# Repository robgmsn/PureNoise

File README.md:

View this project on [CADLAB.io](https://cadlab.io/project/24192). 

# PureNoise

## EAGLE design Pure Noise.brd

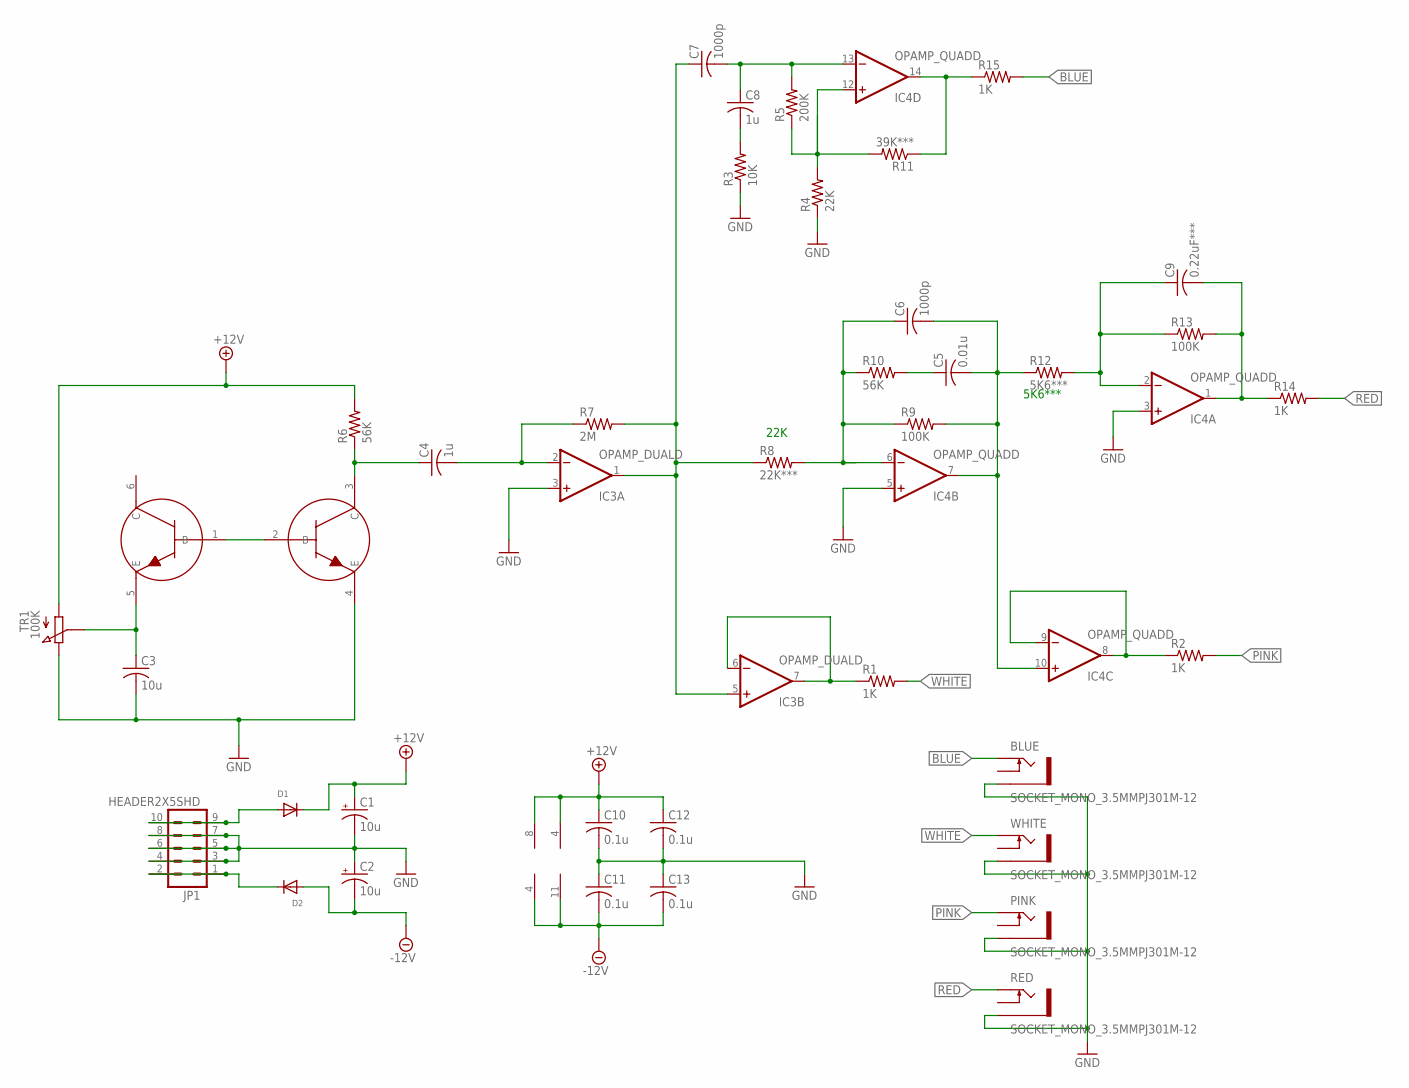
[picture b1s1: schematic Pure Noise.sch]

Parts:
BLUE: SOCKET_MONO_3.5MMPJ301M-12; PJ301M-12
C1, C2: 10u; 153CLV-0505
C3: 10u; C0805
C4, C8: 1u; C0805
C5: 0.01u; C0805
C6, C7: 1000p; C0805
C9: 0.22uF***; C0805
C10, C11, C12, C13: 0.1u; C0805
D1, D2: DIODESMA; SMADIODE
IC3: OPAMP_DUALD; SO08
IC4: OPAMP_QUADD; SO14
JP1: HEADER2X5SHD; 2X5-SHROUDED
PINK: SOCKET_MONO_3.5MMPJ301M-12; PJ301M-12
R1, R2, R14, R15: 1K; R0805
R3: 10K; R0805
R4: 22K; R0805
R5: 200K; R0805
R6, R10: 56K; R0805
R7: 2M; R0805
R8: 22K***; R0805
R9, R13: 100K; R0805
R11: 39K***; R0805
R12: 5K6***; R0805
RED: SOCKET_MONO_3.5MMPJ301M-12; PJ301M-12
T1: TRANSISTOR_PAIR_NPN; TRANS_PAIR
TR1: 100K; TRIMMER_TH
WHITE: SOCKET_MONO_3.5MMPJ301M-12; PJ301M-12

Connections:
+12V: C1.+, C10.1, C12.1, D1.C, IC3.8 (V+), IC4.4 (V+), R6.2, TR1.1
-12V: C2.-, C11.2, C13.2, D2.A, IC3.4 (V-), IC4.11 (V-)
BLUE: BLUE.TIP, R15.2
GND: BLUE.GND (SLEEVE), C1.-, C2.+, C3.2, C10.2, C11.1, C12.2, C13.1, IC3.3 (+IN), IC4.3 (+IN), IC4.5 (+IN), JP1.3, JP1.4, JP1.5, JP1.6, JP1.7, JP1.8, PINK.GND (SLEEVE), R3.1, R4.1, RED.GND (SLEEVE), T1.4 (E), TR1.3, WHITE.GND (SLEEVE)
unnamed: IC3.6 (-IN), IC3.7 (OUT), R1.1
unnamed: IC4.8 (OUT), IC4.9 (-IN), R2.1
unnamed: C8.2, R3.2
unnamed: C7.2, C8.1, IC4.13 (-IN), R5.2
unnamed: IC4.12 (+IN), R4.2, R5.1, R11.2
unnamed: C9.1, IC4.2 (-IN), R12.2, R13.1
unnamed: C9.2, IC4.1 (OUT), R13.2, R14.1
unnamed: D1.A, JP1.9, JP1.10
unnamed: D2.C, JP1.1, JP1.2
unnamed: IC4.14 (OUT), R11.1, R15.1
unnamed: T1.1 (B), T1.2 (B)
unnamed: C3.1, T1.5 (E), TR1.2
unnamed: C4.1, R6.1, T1.3 (C)
unnamed: C4.2, IC3.2 (-IN), R7.1
unnamed: C6.1, IC4.6 (-IN), R8.2, R9.1, R10.1
unnamed: C5.1, R10.2
unnamed: C7.1, IC3.1 (OUT), IC3.5 (+IN), R7.2, R8.1
unnamed: C5.2, C6.2, IC4.7 (OUT), IC4.10 (+IN), R9.2, R12.1
PINK: PINK.TIP, R2.2
RED: R14.2, RED.TIP
WHITE: R1.2, WHITE.TIP

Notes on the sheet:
22K
5K6***

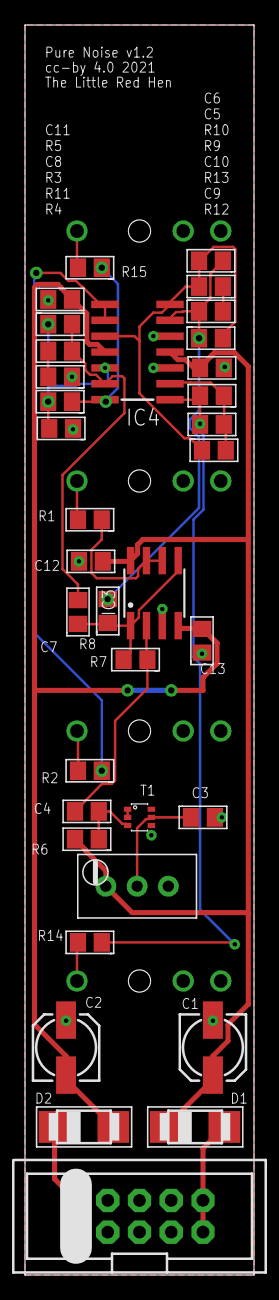
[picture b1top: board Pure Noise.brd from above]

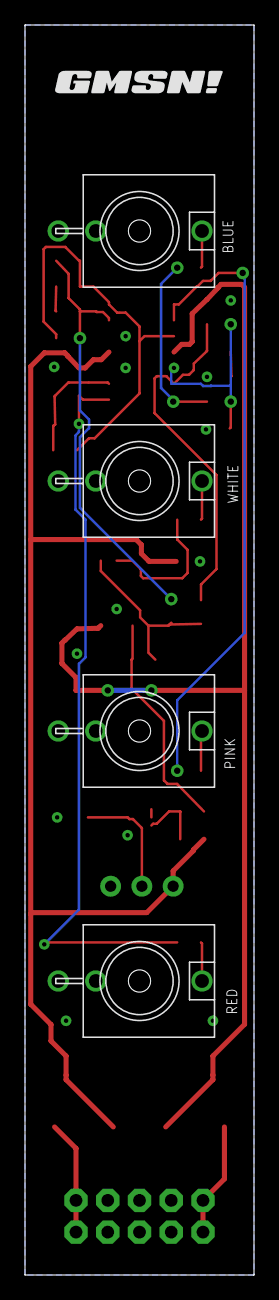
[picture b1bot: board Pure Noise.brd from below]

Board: 2 copper layers, 18.3 x 100.0 mm, 40 parts (5 on the bottom side), 25 nets.

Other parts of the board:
U$3: GMSN!_LOGO

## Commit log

2021-04-16 Noise 1.1
2021-04-16 Revert "Noise 1.1"
    This reverts commit 9391577aeb04c9f39d70b21b663ef0e1ff89b3f4.
2021-04-16 Noise 1.0
2021-04-16 Backlink to CADLAB.io has been added.
2021-07-07 Reinstall

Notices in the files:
Pure Noise.brd:
cc-by 4.0 2021
